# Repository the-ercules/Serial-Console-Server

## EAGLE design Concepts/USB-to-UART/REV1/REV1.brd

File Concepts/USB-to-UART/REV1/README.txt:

The first public revision of this board (there is technically a REV0, but I'm too embarrassed by it to release)

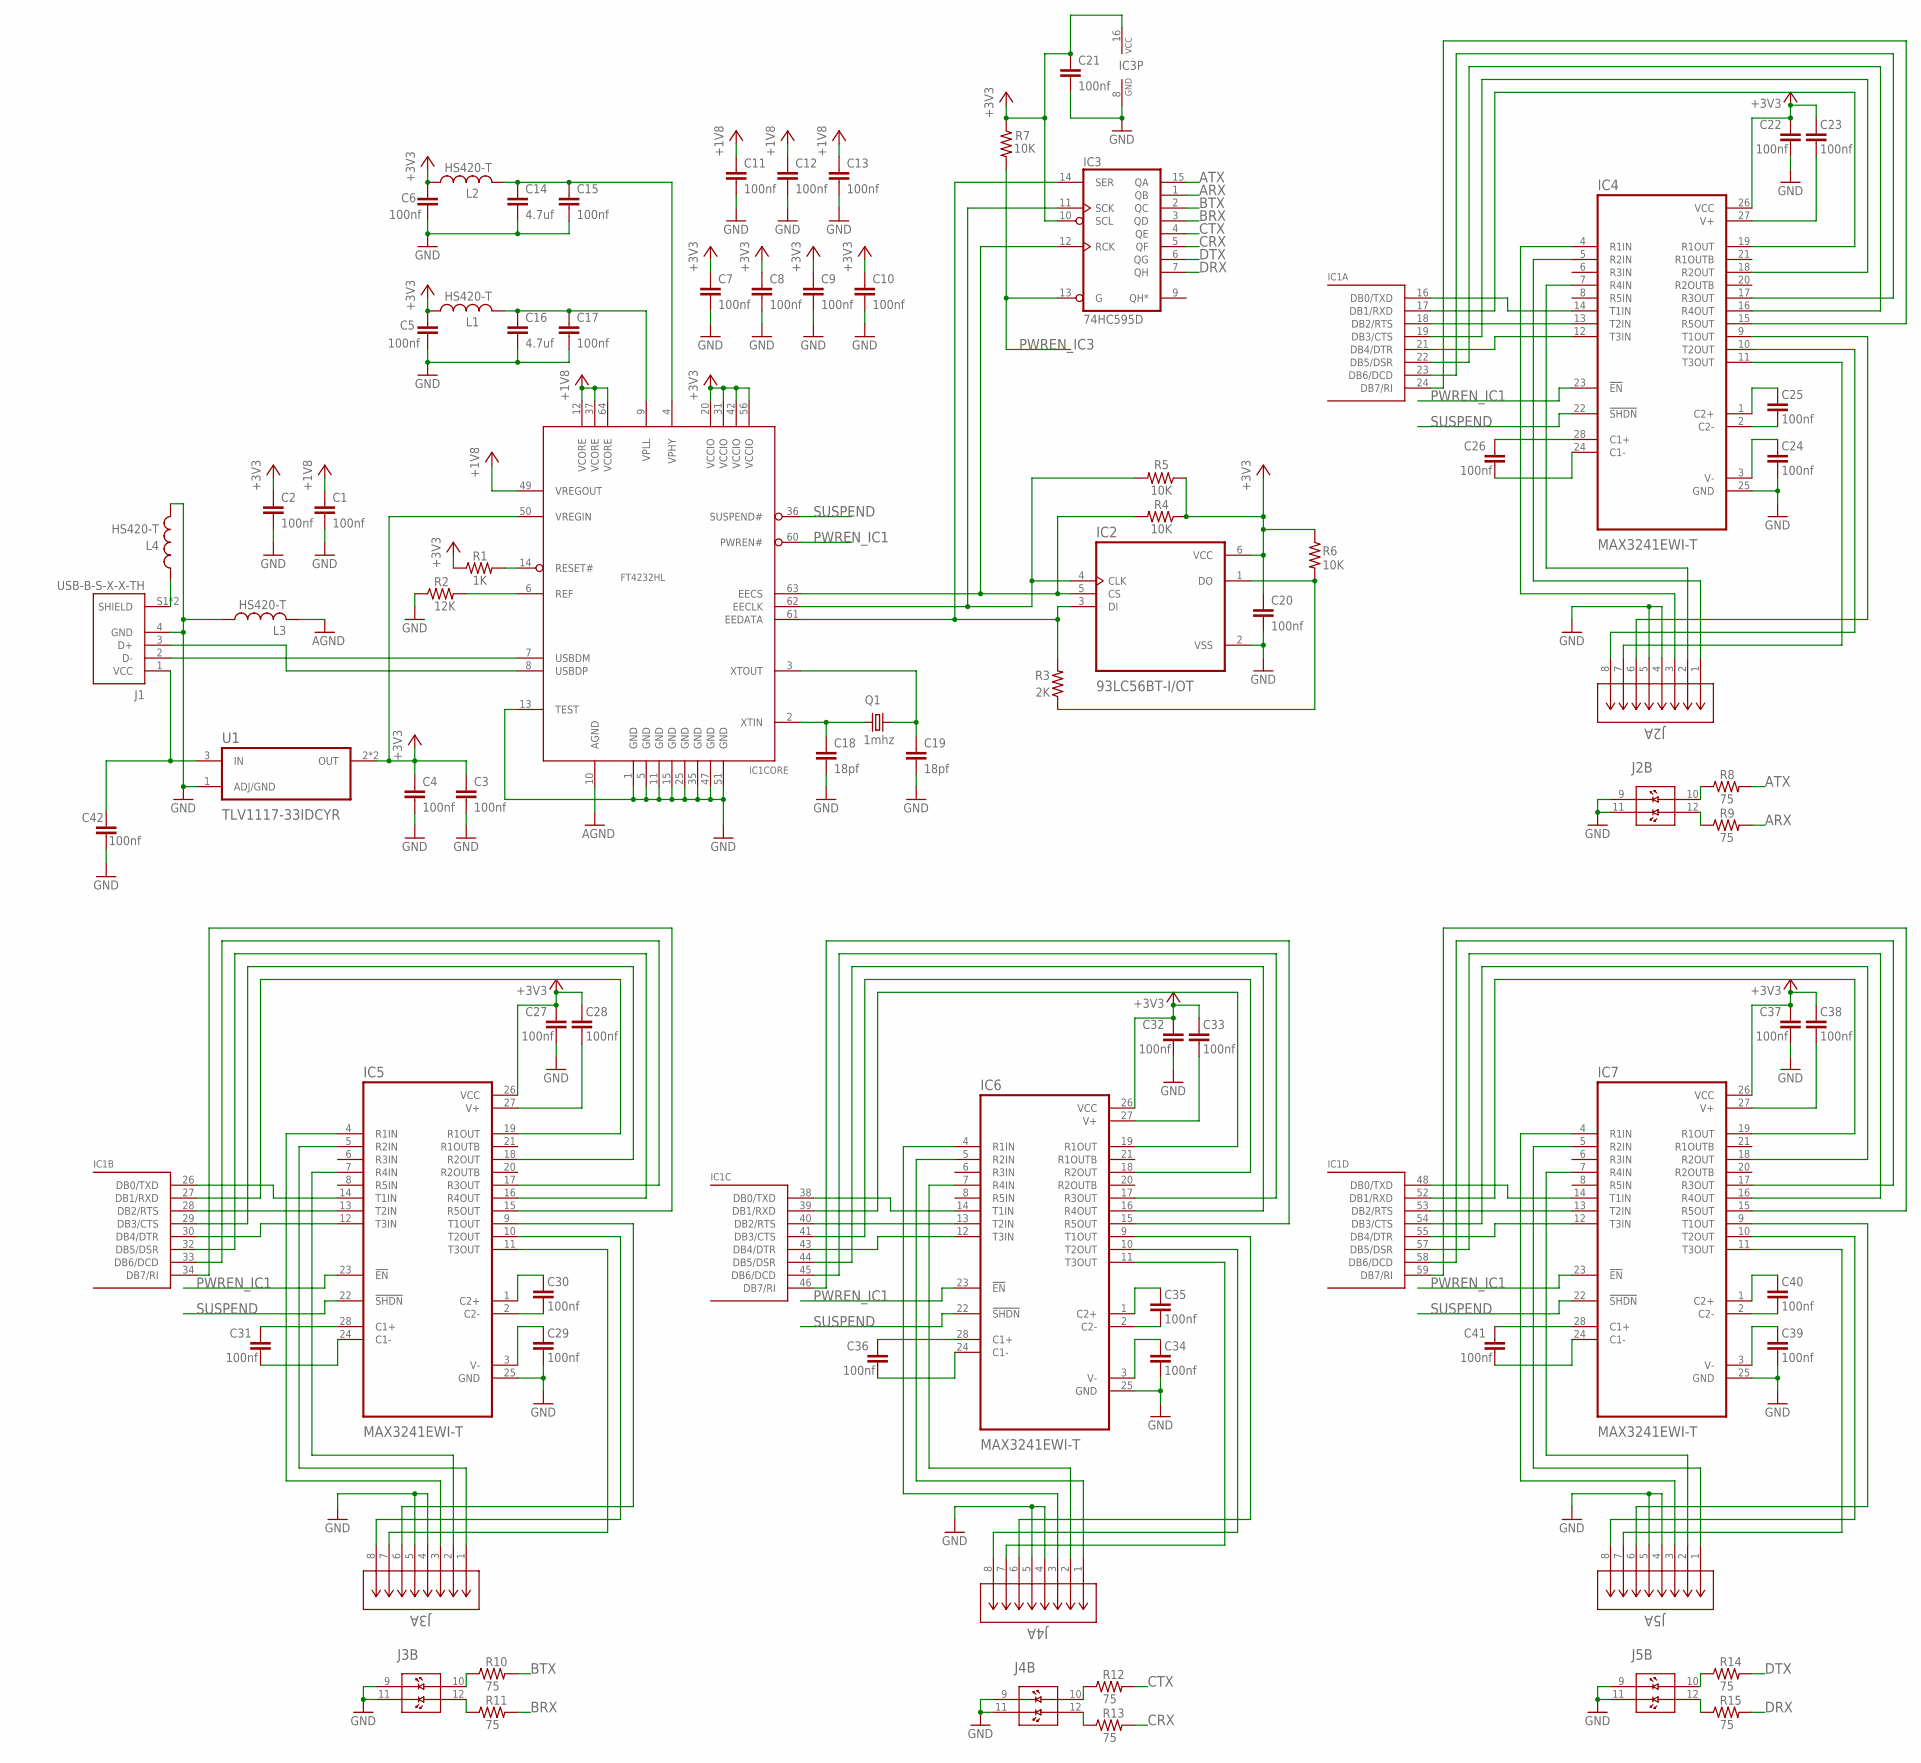
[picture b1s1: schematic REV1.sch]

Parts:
C1, C2, C3, C4, C5, C6, C7, C8, C9, C10, C11, C12, C13, C15, C17, C20, C21, C22, C23, C24, C25, C26, C27, C28, C29, C30, C31, C32, C33, C34, C35, C36, C37, C38, C39, C40, C41, C42: 100nf; C0603
C14, C16: 4.7uf; C0603
C18, C19: 18pf; C0603
IC1: FT4232HL; LQFP64
IC2: 93LC56BT-I/OT; SOT95P280X145-6N
IC3: 74HC595D; SO16
IC4, IC5, IC6, IC7: MAX3241EWI-T; SOIC127P1032X265-28N
J1: USB-B-S-X-X-TH; SAMTEC_USB-B-S-X-X-TH
J2, J3, J4, J5: RJHSE-5384; RJHSE-5384_AMP
L1, L2, L3, L4: HS420-T; L2012C
Q1: 1mhz; HC49/S
R1: 1K; R0805
R2: 12K; R0805
R3: 2K; R0805
R4, R5, R6, R7: 10K; R0805
R8, R9, R10, R11, R12, R13, R14, R15: 75; R0805
U1: TLV1117-33IDCYR; SOT230P700X180-4N

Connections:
+1V8: C1.1, C11.1, C12.1, C13.1, IC1.12 (VCORE), IC1.37 (VCORE), IC1.49 (VREGOUT), IC1.64 (VCORE)
+3V3: C2.1, C3.1, C4.1, C5.1, C6.1, C7.1, C8.1, C9.1, C10.1, C20.1, C21.1, C22.1, C23.1, C27.1, C28.1, C32.1, C33.1, C37.1, C38.1, IC1.20 (VCCIO), IC1.31 (VCCIO), IC1.42 (VCCIO), IC1.50 (VREGIN), IC1.56 (VCCIO), IC2.6 (VCC), IC3.10 (SCL), IC3.16 (VCC), IC4.26 (VCC), IC5.26 (VCC), IC6.26 (VCC), IC7.26 (VCC), L1.1, L2.1, R1.1, R4.1, R5.1, R6.1, R7.1, U1.2 (OUT), U1.4 (OUT)
AGND: IC1.10 (AGND), L3.2
ARX: IC3.1 (QB), R9.2
ATX: IC3.15 (QA), R8.2
BRX: IC3.3 (QD), R11.2
BTX: IC3.2 (QC), R10.2
C1+1: C26.1, IC4.28 (C1+)
C1+2: C31.1, IC5.28 (C1+)
C1+3: C36.1, IC6.28 (C1+)
C1+4: C41.1, IC7.28 (C1+)
C1-1: C26.2, IC4.24 (C1-)
C1-2: C31.2, IC5.24 (C1-)
C1-3: C36.2, IC6.24 (C1-)
C1-4: C41.2, IC7.24 (C1-)
C2+1: C25.1, IC4.1 (C2+)
C2+2: C30.1, IC5.1 (C2+)
C2+3: C35.1, IC6.1 (C2+)
C2+4: C40.1, IC7.1 (C2+)
C2-1: C25.2, IC4.2 (C2-)
C2-2: C30.2, IC5.2 (C2-)
C2-3: C35.2, IC6.2 (C2-)
C2-4: C40.2, IC7.2 (C2-)
CLKIN: C18.1, IC1.2 (XTIN), Q1.2
CLKOUT: C19.1, IC1.3 (XTOUT), Q1.1
CRX: IC3.5 (QF), R13.2
CTS_A: IC4.5 (R2IN), J2.1
CTS_A1: IC5.5 (R2IN), J3.1
CTS_A2: IC6.5 (R2IN), J4.1
CTS_A3: IC7.5 (R2IN), J5.1
CTX: IC3.4 (QE), R12.2
DO: IC2.1 (DO), R3.1, R6.2
DRX: IC3.7 (QH), R15.2
DSR_A: IC4.7 (R4IN), J2.2
DSR_A1: IC5.7 (R4IN), J3.2
DSR_A2: IC6.7 (R4IN), J4.2
DSR_A3: IC7.7 (R4IN), J5.2
DTR_A: IC4.11 (T3OUT), J2.7
DTR_A1: IC5.11 (T3OUT), J3.7
DTR_A2: IC6.11 (T3OUT), J4.7
DTR_A3: IC7.11 (T3OUT), J5.7
DTX: IC3.6 (QG), R14.2
EECLK: IC1.62 (EECLK), IC2.4 (CLK), IC3.11 (SCK), R5.2
EECS: IC1.63 (EECS), IC2.5 (CS), IC3.12 (RCK), R4.2
EEDATA: IC1.61 (EEDATA), IC2.3 (DI), IC3.14 (SER), R3.2
GND: C1.2, C2.2, C3.2, C4.2, C5.2, C6.2, C7.2, C8.2, C9.2, C10.2, C11.2, C12.2, C13.2, C14.2, C15.2, C16.2, C17.2, C18.2, C19.2, C20.2, C21.2, C22.2, C24.2, C27.2, C29.2, C32.2, C34.2, C37.2, C39.2, C42.2, IC1.1 (GND), IC1.5 (GND), IC1.11 (GND), IC1.13 (TEST), IC1.15 (GND), IC1.25 (GND), IC1.35 (GND), IC1.47 (GND), IC1.51 (GND), IC2.2 (VSS), IC3.8 (GND), IC4.25 (GND), IC5.25 (GND), IC6.25 (GND), IC7.25 (GND), J1.4 (GND), J2.4, J2.5, J2.9, J2.11, J3.4, J3.5, J3.9, J3.11, J4.4, J4.5, J4.9, J4.11, J5.4, J5.5, J5.9, J5.11, L3.1, L4.2, R2.1, U1.1 (ADJ/GND)
LED_L1: J2.12, R9.1
LED_L2: J3.12, R11.1
LED_L3: J4.12, R13.1
LED_L4: J5.12, R15.1
LED_R1: J2.10, R8.1
LED_R2: J3.10, R10.1
LED_R3: J4.10, R12.1
LED_R4: J5.10, R14.1
PWREN_IC1: IC1.60 (PWREN#), IC4.23 (!EN), IC5.23 (!EN), IC6.23 (!EN), IC7.23 (!EN)
PWREN_IC3: IC3.13 (G), R7.2
REF: IC1.6 (REF), R2.2
RESET: IC1.14 (RESET#), R1.2
RTS_A: IC4.10 (T2OUT), J2.8
RTS_A1: IC5.10 (T2OUT), J3.8
RTS_A2: IC6.10 (T2OUT), J4.8
RTS_A3: IC7.10 (T2OUT), J5.8
RXD_A: IC4.4 (R1IN), J2.3
RXD_A1: IC5.4 (R1IN), J3.3
RXD_A2: IC6.4 (R1IN), J4.3
RXD_A3: IC7.4 (R1IN), J5.3
SUSPEND: IC1.36 (SUSPEND#), IC4.22 (!SHDN), IC5.22 (!SHDN), IC6.22 (!SHDN), IC7.22 (!SHDN)
TTL_CTS_A: IC1.19 (DB3/CTS), IC4.18 (R2OUT)
TTL_CTS_A1: IC1.29 (DB3/CTS), IC5.18 (R2OUT)
TTL_CTS_A2: IC1.41 (DB3/CTS), IC6.18 (R2OUT)
TTL_CTS_A3: IC1.54 (DB3/CTS), IC7.18 (R2OUT)
TTL_DCD_A: IC1.23 (DB6/DCD), IC4.17 (R3OUT)
TTL_DCD_A1: IC1.33 (DB6/DCD), IC5.17 (R3OUT)
TTL_DCD_A2: IC1.45 (DB6/DCD), IC6.17 (R3OUT)
TTL_DCD_A3: IC1.58 (DB6/DCD), IC7.17 (R3OUT)
TTL_DSR_A: IC1.22 (DB5/DSR), IC4.16 (R4OUT)
TTL_DSR_A1: IC1.32 (DB5/DSR), IC5.16 (R4OUT)
TTL_DSR_A2: IC1.44 (DB5/DSR), IC6.16 (R4OUT)
TTL_DSR_A3: IC1.57 (DB5/DSR), IC7.16 (R4OUT)
TTL_DTR_A: IC1.21 (DB4/DTR), IC4.12 (T3IN)
TTL_DTR_A1: IC1.30 (DB4/DTR), IC5.12 (T3IN)
TTL_DTR_A2: IC1.43 (DB4/DTR), IC6.12 (T3IN)
TTL_DTR_A3: IC1.55 (DB4/DTR), IC7.12 (T3IN)
TTL_RI_A: IC1.24 (DB7/RI), IC4.15 (R5OUT)
TTL_RI_A1: IC1.34 (DB7/RI), IC5.15 (R5OUT)
TTL_RI_A2: IC1.46 (DB7/RI), IC6.15 (R5OUT)
TTL_RI_A3: IC1.59 (DB7/RI), IC7.15 (R5OUT)
TTL_RTS_A: IC1.18 (DB2/RTS), IC4.13 (T2IN)
TTL_RTS_A1: IC1.28 (DB2/RTS), IC5.13 (T2IN)
TTL_RTS_A2: IC1.40 (DB2/RTS), IC6.13 (T2IN)
TTL_RTS_A3: IC1.53 (DB2/RTS), IC7.13 (T2IN)
TTL_RXD_A: IC1.17 (DB1/RXD), IC4.19 (R1OUT)
TTL_RXD_A1: IC1.27 (DB1/RXD), IC5.19 (R1OUT)
TTL_RXD_A2: IC1.39 (DB1/RXD), IC6.19 (R1OUT)
TTL_RXD_A3: IC1.52 (DB1/RXD), IC7.19 (R1OUT)
TTL_TXD_A: IC1.16 (DB0/TXD), IC4.14 (T1IN)
TTL_TXD_A1: IC1.26 (DB0/TXD), IC5.14 (T1IN)
TTL_TXD_A2: IC1.38 (DB0/TXD), IC6.14 (T1IN)
TTL_TXD_A3: IC1.48 (DB0/TXD), IC7.14 (T1IN)
TXD_A: IC4.9 (T1OUT), J2.6
TXD_A1: IC5.9 (T1OUT), J3.6
TXD_A2: IC6.9 (T1OUT), J4.6
TXD_A3: IC7.9 (T1OUT), J5.6
USB5V: C42.1, J1.1 (VCC), U1.3 (IN)
USBD_N: IC1.7 (USBDM), J1.2 (D-)
USBD_P: IC1.8 (USBDP), J1.3 (D+)
USBSHLD: J1.S1 (SHIELD), J1.S2 (SHIELD), L4.1
V+1: C23.2, IC4.27 (V+)
V+2: C28.2, IC5.27 (V+)
V+3: C33.2, IC6.27 (V+)
V+4: C38.2, IC7.27 (V+)
V-1: C24.1, IC4.3 (V-)
V-2: C29.1, IC5.3 (V-)
V-3: C34.1, IC6.3 (V-)
V-4: C39.1, IC7.3 (V-)
VPHY: C14.1, C15.1, IC1.4 (VPHY), L2.2
VPLL: C16.1, C17.1, IC1.9 (VPLL), L1.2

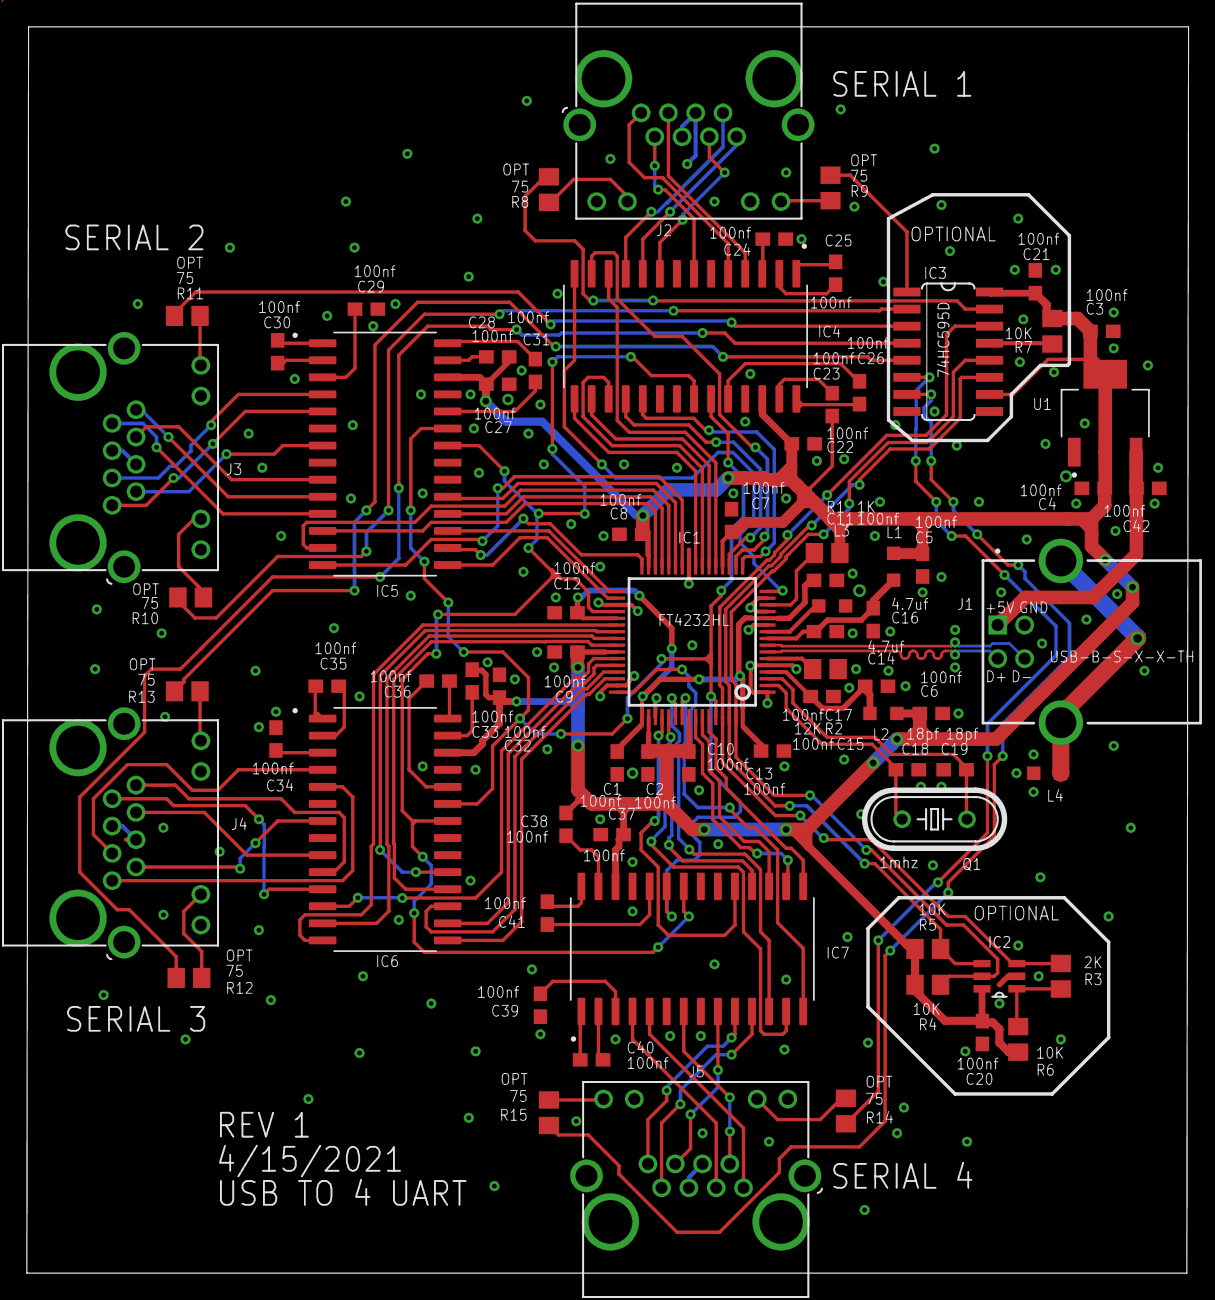
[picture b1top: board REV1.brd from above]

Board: 2 copper layers, 86.5 x 92.8 mm, 75 parts (0 on the bottom side), 117 nets.

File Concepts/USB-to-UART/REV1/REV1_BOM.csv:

"Qty";"Value";"Device";"Package";"Parts";"Description";"AVAILABILITY";"BUILT_BY";"COPYRIGHT";"DATASHEET";"DESCRIPTION";"DIGI-KEY_PART_NUMBER";"MANUFACTURER_PART_NUMBER";"MF";"MP";"MPN";"OC_FARNELL";"OC_NEWARK";"PACKAGE";"POPULARITY";"PRICE";"PURCHASE-URL";"SOURCELIBRARY";"SPICEPREFIX";"VENDOR";
"38";"100nf";"C-EUC0603";"C0603";"C1, C2, C3, C4, C5, C6, C7, C8, C9, C10, C11, C12, C13, C15, C17, C20, C21, C22, C23, C24, C25, C26, C27, C28, C29, C30, C31, C32, C33, C34, C35, C36, C37, C38, C39, C40, C41, C42";"CAPACITOR, European symbol";"";"";"";"";"";"";"";"";"";"";"";"";"";"73";"";"";"";"C";"";
"4";"10K";"R-US_R0805";"R0805";"R4, R5, R6, R7";"RESISTOR, American symbol";"";"";"";"";"";"";"";"";"";"";"";"";"";"85";"";"";"";"R";"";
"1";"12K";"R-US_R0805";"R0805";"R2";"RESISTOR, American symbol";"";"";"";"";"";"";"";"";"";"";"";"";"";"85";"";"";"";"R";"";
"2";"18pf";"C-EUC0603";"C0603";"C18, C19";"CAPACITOR, European symbol";"";"";"";"";"";"";"";"";"";"";"";"";"";"73";"";"";"";"C";"";
"1";"1K";"R-US_R0805";"R0805";"R1";"RESISTOR, American symbol";"";"";"";"";"";"";"";"";"";"";"";"";"";"85";"";"";"";"R";"";
"1";"1mhz";"CRYSTALHC49S";"HC49/S";"Q1";"CRYSTAL";"";"";"";"";"";"";"";"";"";"";"1667008";"unknown";"";"49";"";"";"";"";"";
"1";"2K";"R-US_R0805";"R0805";"R3";"RESISTOR, American symbol";"";"";"";"";"";"";"";"";"";"";"";"";"";"85";"";"";"";"R";"";
"2";"4.7uf";"C-EUC0603";"C0603";"C14, C16";"CAPACITOR, European symbol";"";"";"";"";"";"";"";"";"";"";"";"";"";"73";"";"";"";"C";"";
"1";"74HC595D";"74HC595D";"SO16";"IC3";"8-bit SHIFT REGISTER, output latch";"";"";"";"";"";"";"";"";"";"";"";"";"";"21";"";"";"";"";"";
"8";"75";"R-US_R0805";"R0805";"R8, R9, R10, R11, R12, R13, R14, R15";"RESISTOR, American symbol";"";"";"";"";"";"";"";"";"";"";"";"";"";"85";"";"";"";"R";"";
"1";"93LC56BT-I/OT";"93LC56BT-I/OT";"SOT95P280X145-6N";"IC2";"";"";"";"";"";" IC EEPROM 2K SPI 2MHZ SOT23-6 ";"";"";"Microchip Technology";"93LC56BT-I/OT";"";"";"";"None";"";"";"https://pricing.snapeda.com/search/part/93LC56BT-I/OT/?ref=eda";"";"";"";
"1";"FT4232HL";"FT4232HL";"LQFP64";"IC1";"Quad USB UART";"";"";"";"";"";"";"";"";"";"";"";"";"";"";"";"";"";"";"";
"4";"HS420-T";"L-USL2012C";"L2012C";"L1, L2, L3, L4";"INDUCTOR, American symbol";"";"";"";"";"";"";"";"";"";"";"";"";"";"6";"";"";"";"L";"";
"4";"MAX3241EWI-T";"MAX3241EWI-T";"SOIC127P1032X265-28N";"IC4, IC5, IC6, IC7";"";"";"";"";"";"  3/5 Transceiver Full RS232 28-SOIC ";"MAX3241EWI+T-ND";"";"Maxim Integrated";"MAX3241EWI+";"";"";"";"SOIC-28 Maxim";"";"";"https://pricing.snapeda.com/search/part/MAX3241EWI+/?ref=eda";"";"";"";
"4";"RJHSE-5384";"RJHSE-5384";"RJHSE-5384_AMP";"J2, J3, J4, J5";"";"";"EMA_Cory";"Copyright (C) 2018 Accelerated Designs. All rights reserved";"https://cdn.amphenol-icc.com/media/wysiwyg/files/drawing/rjh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";"";"";"RJHSE-5384";"";"";"";"";"";"";"";"";"";"Amphenol_2020-10-07";"";"Amphenol";
"1";"TLV1117-33IDCYR";"TLV1117-33IDCYR";"SOT230P700X180-4N";"U1";"";"";"";"";"";" 800-mA, 15-V, linear voltage regulator 4-SOT-223 -40 to 125 ";"296-21113-1-ND";"";"Texas Instruments";"TLV1117-33IDCYR";"";"";"";"SOT-223-4 Texas Instruments";"";"";"https://pricing.snapeda.com/search/part/TLV1117-33IDCYR/?ref=eda";"";"";"";
"1";"USB-B-S-X-X-TH";"USB-B-S-X-X-TH";"SAMTEC_USB-B-S-X-X-TH";"J1";"USB-B (USB TYPE-B) USB 2.0 Receptacle Connector 4 Position Through Hole, Right Angle Check prices";"Warning";"";"";"";" USB-B (USB TYPE-B) USB 2.0 Receptacle Connector 4 Position Through Hole, Right Angle ";"";"";"Samtec";"USB-B-S-S-B-TH";"";"";"";"None";"";"None";"https://pricing.snapeda.com/search/part/USB-B-S-S-B-TH/?ref=eda";"";"";"";

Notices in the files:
Concepts/USB-to-UART/REV1/REV1_BOM.csv:
"RJHSE-5384";"RJHSE-5384";"RJHSE-5384_AMP";"J2, J3, J4, J5";"";"";"EMA_Cory";"Copyright (C) 2018 Accelerated Designs. All rights reserved";"https://cdn.amphenol-icc.com/media/wysiwyg/files/drawing/rjhsex38x.pdf";"";"";"RJHSE-5384";"";"";"";"";"";"";"";"";"";"Amphenol_2020-10-07";"";"Amphenol";
parts and their libraries:
COPYRIGHT: Copyright (C) 2018 Accelerated Designs. All rights reserved
